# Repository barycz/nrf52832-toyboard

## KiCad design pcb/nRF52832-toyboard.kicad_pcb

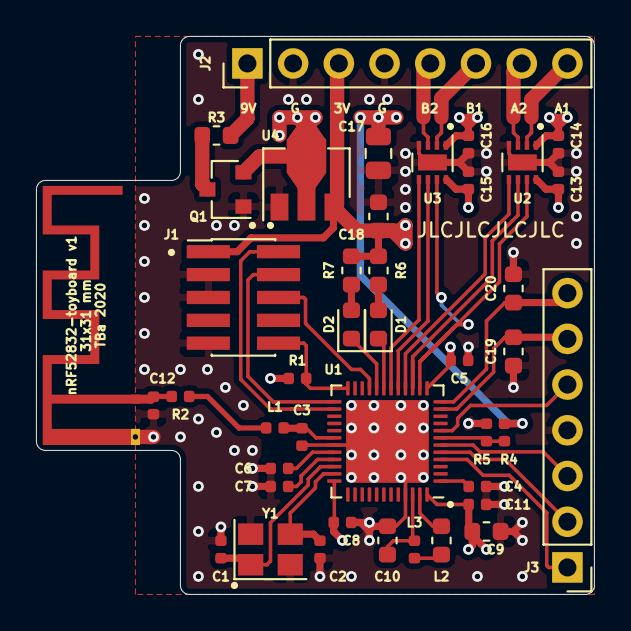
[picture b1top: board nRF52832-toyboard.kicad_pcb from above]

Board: 4 copper layers, 31.0 x 31.0 mm, 42 parts (0 on the bottom side), 40 nets.

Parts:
AE1: Antenna; Texas_SWRA117D_2.4GHz_Right
C1, C2: 12p; C_0402_1005Metric
C3: 1p; C_0402_1005Metric
C4, C5, C8, C11, C13, C14, C15, C16: 100n; C_0402_1005Metric
C6: DNP; C_0402_1005Metric
C7: 100p; C_0402_1005Metric
C9: 4.7u; C_0603_1608Metric
C10: 1u; C_0603_1608Metric
C12: 1.5p; C_0402_1005Metric
C17: 10u; C_0805_2012Metric
C18: 10u; C_0603_1608Metric
C19, C20: DNP; C_0603_1608Metric
D1: BLUE; LED_0603_1608Metric
D2: RED; LED_0603_1608Metric
J1: Conn_ARM_JTAG_SWD_10; PinHeader_2x05_P1.27mm_Vertical_SMD
J2: Conn_01x08; PinHeader_1x08_P2.54mm_Vertical
J3: Conn_01x07; PinHeader_1x07_P2.54mm_Vertical
L1: 3.9n; L_0402_1005Metric
L2: 10u; L_0603_1608Metric
L3: 15n; L_0402_1005Metric
Q1: AO3401A; SOT-23
R1: 10k; R_0402_1005Metric
R2: 0; R_0402_1005Metric
R3: 0; R_0603_1608Metric
R4: 470k; R_0402_1005Metric
R5: 220k; R_0402_1005Metric
R6, R7: 1k; R_0603_1608Metric
U1: nRF52832-QFxx; QFN-48-1EP_6x6mm_P0.4mm_EP4.6x4.6mm
U2, U3: DRV8837; WSON-8-1EP_2x2mm_P0.5mm_EP0.9x1.6mm
U4: HT75xx-1-SOT89; SOT-89-3
Y1: 32MHz; Crystal_SMD_3225-4Pin_3.2x2.5mm

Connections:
+3V3: C5.1, C8.1, C9.1, C11.1, C13.1, C15.1, C18.1, J1.1, J2.3, R1.1, R6.1, R7.1, U1.13, U1.36, U1.48, U2.8, U3.8, U4.3
+9V: J2.1, R3.1
AIN0: J3.1, U1.4
AIN1: J3.2, U1.5
AIN2: J3.3, U1.6
AIN3: R4.2, R5.1, U1.7
DCC: L2.1, U1.47
DEC1: C4.1, U1.1
DEC2: C6.1, U1.32
DEC3: C7.1, U1.33
DEC4: C10.1, L3.2, U1.46
DRVAIN1: U1.15, U2.6
DRVAIN2: U1.16, U2.5
DRVBIN1: U1.17, U3.6
DRVBIN2: U1.18, U3.5
GND: AE1.2, C1.2, C2.2, C3.2, C4.2, C5.2, C6.2, C7.2, C8.2, C9.2, C10.2, C11.2, C12.2, C13.2, C14.2, C15.2, C16.2, C17.2, C18.2, C19.1, C20.2, J1.3, J1.5, J1.9, J2.2, J2.4, J3.4, Q1.1, R5.2, U1.31, U1.45, U1.49, U2.4, U2.9, U3.4, U3.9, U4.1, Y1.2, Y1.4
NBLED: D1.1, U1.19
NDRVSLEEP: U1.14, U2.7, U3.7
NFC1: C19.2, J3.6, U1.11
NFC2: C20.1, J3.7, U1.12
NRLED: D2.1, U1.20
unnamed: AE1.1, C12.1, R2.1
unnamed: C1.1, U1.34, Y1.1
unnamed: C2.1, U1.35, Y1.3
unnamed: C3.1, L1.2, U1.30
unnamed: D1.2, R6.2
unnamed: D2.2, R7.2
unnamed: L2.2, L3.1
unnamed: Q1.3, R3.2
OUTA1: J2.8, U2.2
OUTA2: J2.7, U2.3
OUTB1: J2.6, U3.2
OUTB2: J2.5, U3.3
P006: J3.5, U1.8
RF: L1.1, R2.2
SWDCLK: J1.4, U1.25
SWDIO: J1.2, U1.26
SWO: J1.6, U1.21
Vin: C14.1, C16.1, C17.1, Q1.2, R4.1, U2.1, U3.1, U4.2
nRST: J1.10, R1.2, U1.24

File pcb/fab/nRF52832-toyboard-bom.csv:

Comment,Designator,Footprint,LCSC, LCSC, note
"Antenna","AE1","RF_Antenna:Texas_SWRA117D_2.4GHz_Right",""
"12p","C1,C2","Capacitor_SMD:C_0402_1005Metric","","C1547",""
"1u","C10","Capacitor_SMD:C_0603_1608Metric","","C15849",""
"1.5p","C12","Capacitor_SMD:C_0402_1005Metric","","C1552","should be 1.2p for this package"
"10u","C17","Capacitor_SMD:C_0805_2012Metric","","C15850",""
"10u","C18","Capacitor_SMD:C_0603_1608Metric","","C19702",""
"DNP","C19,C20","Capacitor_SMD:C_0603_1608Metric",""
"1p","C3","Capacitor_SMD:C_0402_1005Metric","","C1550","should be 0.8p for this package"
"100n","C5,C8,C4,C11,C13,C14,C15,C16","Capacitor_SMD:C_0402_1005Metric","","C1525",""
"DNP","C6","Capacitor_SMD:C_0402_1005Metric",""
"100p","C7","Capacitor_SMD:C_0402_1005Metric","","C1546",""
"4.7u","C9","Capacitor_SMD:C_0603_1608Metric","","C19666",""
"BLUE","D1","LED_SMD:LED_0603_1608Metric","","C72041",""
"RED","D2","LED_SMD:LED_0603_1608Metric","","C2286",""
"Conn_ARM_JTAG_SWD_10","J1","Connector_PinHeader_1.27mm:PinHeader_2x05_P1.27mm_Vertical_SMD",""
"Conn_01x08","J2","Connector_PinHeader_2.54mm:PinHeader_1x08_P2.54mm_Vertical",""
"Conn_01x07","J3","Connector_PinHeader_2.54mm:PinHeader_1x07_P2.54mm_Vertical",""
"3.9n","L1","Inductor_SMD:L_0402_1005Metric","","C14033",""
"10u","L2","Inductor_SMD:L_0603_1608Metric","","C1035",""
"15n","L3","Inductor_SMD:L_0402_1005Metric","","C27143",""
"AO3401A","Q1","Package_TO_SOT_SMD:SOT-23","","C15127",""
"10k","R1","Resistor_SMD:R_0402_1005Metric","","C25744",""
"0","R2","Resistor_SMD:R_0402_1005Metric","","C17168",""
"0","R3","Resistor_SMD:R_0603_1608Metric","","C21189",""
"470k","R4","Resistor_SMD:R_0402_1005Metric","","C25790",""
"220k","R5","Resistor_SMD:R_0402_1005Metric","","C25767",""
"1k","R6,R7","Resistor_SMD:R_0603_1608Metric","","C21190",""
"nRF52832-QFxx","U1","Package_DFN_QFN:QFN-48-1EP_6x6mm_P0.4mm_EP4.6x4.6mm","","C77540",""
"DRV8837","U2,U3","Package_SON:WSON-8-1EP_2x2mm_P0.5mm_EP0.9x1.6mm","","C39159",""
"HT75xx-1-SOT89","U4","Package_TO_SOT_SMD:SOT-89-3","","C14289",""
"32MHz","Y1","Crystal:Crystal_SMD_3225-4Pin_3.2x2.5mm","","C113671",""

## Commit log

2020-12-15 initialize repo with working BLE beacon
2020-12-18 add simple testing central web app
2020-12-18 add leds and custom ble service
2020-12-20 direct access to the output of the driver
2020-12-20 add battery voltage service
2020-12-20 support more peripherals in controller
2020-12-26 add motor driver
2021-01-17 tweak battery values
2021-01-17 slow advertising
2021-01-17 enable power management
2021-01-17 enable pwm and add to dts
2021-01-17 pwm controlled outputs
2021-01-20 slower pwm
2021-01-20 updated motor driver protocol
2021-01-21 remove obsoelte ctrl methods, also throw on connection fail
2021-02-04 battery in the UI
2021-02-05 add doc and pcb
2021-02-07 view refactor
2021-02-07 arrow and checks
2021-02-08 styles
2021-02-08 big duty steps
2021-02-10 nvs configuration
2021-02-10 cosmetic changes
2021-02-10 config ui
